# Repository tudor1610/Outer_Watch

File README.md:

<small>Copyright @Tudor Brandibur 2025-2026</small>

# Outer Watch

This repository contains the project for Outer_Watch, a smart watch based on the nRF52840 microcontroller, designed for power efficiency and Bluetooth Low Energy (BLE) connectivity.

## 1. Block diagram

## 2. BOM
| Designator | Qty | Component | Package | Description | Part number | Datasheet/Link |
| :--- | :---: | :--- | :--- | :--- | :--- | :--- |
| U1 | 1 | nRF52840 | aQFN-73 | Main Bluetooth 5.4 SoC | [C190733](https://www.lcsc.com/product-detail/C190733.html) | [View](https://www.lcsc.com/product-detail/C190733.html) |
| IC1 | 1 | BQ25180YBGR | DSBGA-8 | Battery Charge Management IC | [C5186637](https://www.lcsc.com/product-detail/C5186637.html) | [View](https://www.lcsc.com/product-detail/C5186637.html) |
| IC9 | 1 | RT6160AWSC | WL-CSP-15 | High-Efficiency Buck-Boost | [C464871](https://www.lcsc.com/product-detail/C464871.html) | [View](https://www.lcsc.com/product-detail/C464871.html) |
| IC3 | 1 | BMA423 | LGA-12 | 3-axis Accelerometer | [C128221](https://www.lcsc.com/product-detail/C128221.html) | [View](https://www.lcsc.com/product-detail/C128221.html) |
| U3 | 1 | MAX17048G+T10 | TDFN-8 | Battery Fuel Gauge | [C51509](https://www.lcsc.com/product-detail/C51509.html) | [View](https://www.lcsc.com/product-detail/C51509.html) |
| IC2 | 1 | DRV2605YZFR | DSBGA-9 | Haptic Driver | [C60367](https://www.lcsc.com/product-detail/C60367.html) | [View](https://www.lcsc.com/product-detail/C60367.html) |
| J4 | 1 | KH-TYPE-C-16P | SMD | USB-C 16-Pin Connector | [C3111425](https://www.lcsc.com/product-detail/C3111425.html) | [View](https://www.lcsc.com/product-detail/C3111425.html) |
| J1 | 1 | 503480-2400 | SMD | 24-Pin FPC Connector | [C193568](https://www.lcsc.com/product-detail/C193568.html) | [View](https://www.lcsc.com/product-detail/C193568.html) |
| ANT1 | 1 | 2450AT18B100E | 1206 | 2.4GHz Chip Antenna | [C96245](https://www.lcsc.com/product-detail/C96245.html) | [View](https://www.lcsc.com/product-detail/C96245.html) |
| D3 | 1 | USBLC6-2SC6Y | SOT-23-6 | ESD Protection | [C314115](https://www.lcsc.com/product-detail/C314115.html) | [View](https://www.lcsc.com/product-detail/C314115.html) |
| Q1 | 1 | DMG2305UX-7 | SOT-23 | P-Channel MOSFET | [C131015](https://www.lcsc.com/product-detail/C131015.html) | [View](https://www.lcsc.com/product-detail/C131015.html) |
| Q3 | 1 | SI1308EDL-T1-GE3 | SOT-323 | N-Channel MOSFET 30V | [C139044](https://www.lcsc.com/product-detail/C139044.html) | [View](https://www.lcsc.com/product-detail/C139044.html) |
| D2, D4, D5 | 3 | MBR0530 | SOD-123 | Schottky Rectifier | [C2053](https://www.lcsc.com/product-detail/C2053.html) | [View](https://www.lcsc.com/product-detail/C2053.html) |
| X1 | 1 | ABM11-27MHz | 2016 | 27MHz HF Crystal | [C529322](https://www.lcsc.com/product-detail/C529322.html) | [View](https://www.lcsc.com/product-detail/C529322.html) |
| X2 | 1 | LFXTAL061361 | 3215 | 32.768kHz RTC Crystal | [C104780](https://www.lcsc.com/product-detail/C104780.html) | [View](https://www.lcsc.com/product-detail/C104780.html) |
| L7 | 1 | MLP2016SR47M | 0806 | 0.47uH Power Inductor | [C45943](https://www.lcsc.com/product-detail/C45943.html) | [View](https://www.lcsc.com/product-detail/C45943.html) |
| L5 | 1 | 744043680 | SMD | 68uH Shielded Inductor | [C19438](https://www.lcsc.com/product-detail/C19438.html) | [View](https://www.lcsc.com/product-detail/C19438.html) |
| L2, L3 | 2 | ATFC-0402-3N3 | 0402 | 3.3nH High Q Inductor | [C529323](https://www.lcsc.com/product-detail/C529323.html) | [View](https://www.lcsc.com/product-detail/C529323.html) |
| R-Group | 15 | CPF0201D7K68C1 | 0201 | Precision Resistors | [C420120](https://www.lcsc.com/product-detail/C420120.html) | [View](https://www.lcsc.com/product-detail/C420120.html) |
| C-0402 | 25 | C0402C333J4REC | 0402 | MLCC Capacitors | [C418932](https://www.lcsc.com/product-detail/C418932.html) | [View](https://www.lcsc.com/product-detail/C418932.html) |
| C-0201 | 26 | 02016D105KAT2A | 0201 | X5R 1.0uF Capacitors | [C293021](https://www.lcsc.com/product-detail/C293021.html) | [View](https://www.lcsc.com/product-detail/C293021.html) |
| C-Ultra | 4 | GRM011R60J152 | 01005 | Ultra-Small Capacitors | [C293022](https://www.lcsc.com/product-detail/C293022.html) | [View](https://www.lcsc.com/product-detail/C293022.html) |

## 3. Hardware Description

#### Modules and Functionality
Microcontroller (SoC): nRF52840 (Cortex-M4F at 64MHz). It offers native support for USB, Bluetooth 5, and ultra-low power consumption in sleep modes.

#### Sensors
Integrated motion sensor (IMU) for features like "Lift to Wake" and step counting.

#### Power Management
Battery charging is handled by the TP4056 circuit powered via USB-C. Voltage is regulated to 3.3V through the RT9193 LDO regulator.

#### Communication Interfaces
I2C: Used for the Display and IMU (Standard 400kHz speed).

SWD: Programming and debugging interface (SWDIO and SWDCLK pins).

USB: For charging and data communication/DFU.

### Power Consumption (Estimation)
Deep Sleep (System OFF): ~3uA (nRF52840) + ~2uA (IMU sleep) = ~5uA.

Active Mode (Screen ON + BLE): ~15mA - 20mA.

Battery Life: With a 200mAh battery, under mixed usage, the watch can operate between 5 to 10 days.

## 4. Hardware Mapping & Pin Configuration
The nRF52840 acts as the central brain. Below is the pin allocation strategy used to balance signal integrity, power consumption, and peripheral speed.
1. Communication Buses (I2C & SPI)

- Display (SPI): P0.17 (SCK), P0.20 (MOSI), P0.15 (CS), P0.22 (DC), P0.24 (RST)
- Sensors & Power (I2C): P0.26 (SDA), P0.27 (SCL)

2. Specialized Integrated Circuits (ICs)

- BMA423 (Accelerometer): P0.11 (INT1): Used for Wake-on-Motion. This allows the nRF52840 to stay in "System ON" low-power mode until a wrist tilt or tap is detected.

- MAX17048 (Fuel Gauge): 0.26/P0.27: Reads battery VCELL and SOC (State of Charge). No external sense resistor is needed due to the ModelGauge algorithm.

- BQ25180 (Charger): P0.13 (INT): Signals charging status changes (cable connected, charging complete).

- DRV2605L (Haptic Driver): P0.14 (EN): Enables the chip. Controlled via I2C to trigger complex ERM/LRA vibration patterns for notifications.

3. Power & Interaction
- Navigation Switches (SW_UP, SW_DW, SW_ENT): P1.02, P1.04, P1.06: Connected to GPIOs with internal Pull-Up resistors. These pins on Port 1 are used to keep Port 0 free for high-speed serial traces.

- USB Interface: D+ / D-: Dedicated hardware pins on the nRF52840. Used for the USB stack (CDC/MSC) without consuming standard GPIOs.

4. RF & Clock (Critical Traces)

- 2.4GHz Antenna: ANT

- HF Crystal (27MHz): XC1, XC2

- LF Crystal (32.768kHz): P0.00, P0.01

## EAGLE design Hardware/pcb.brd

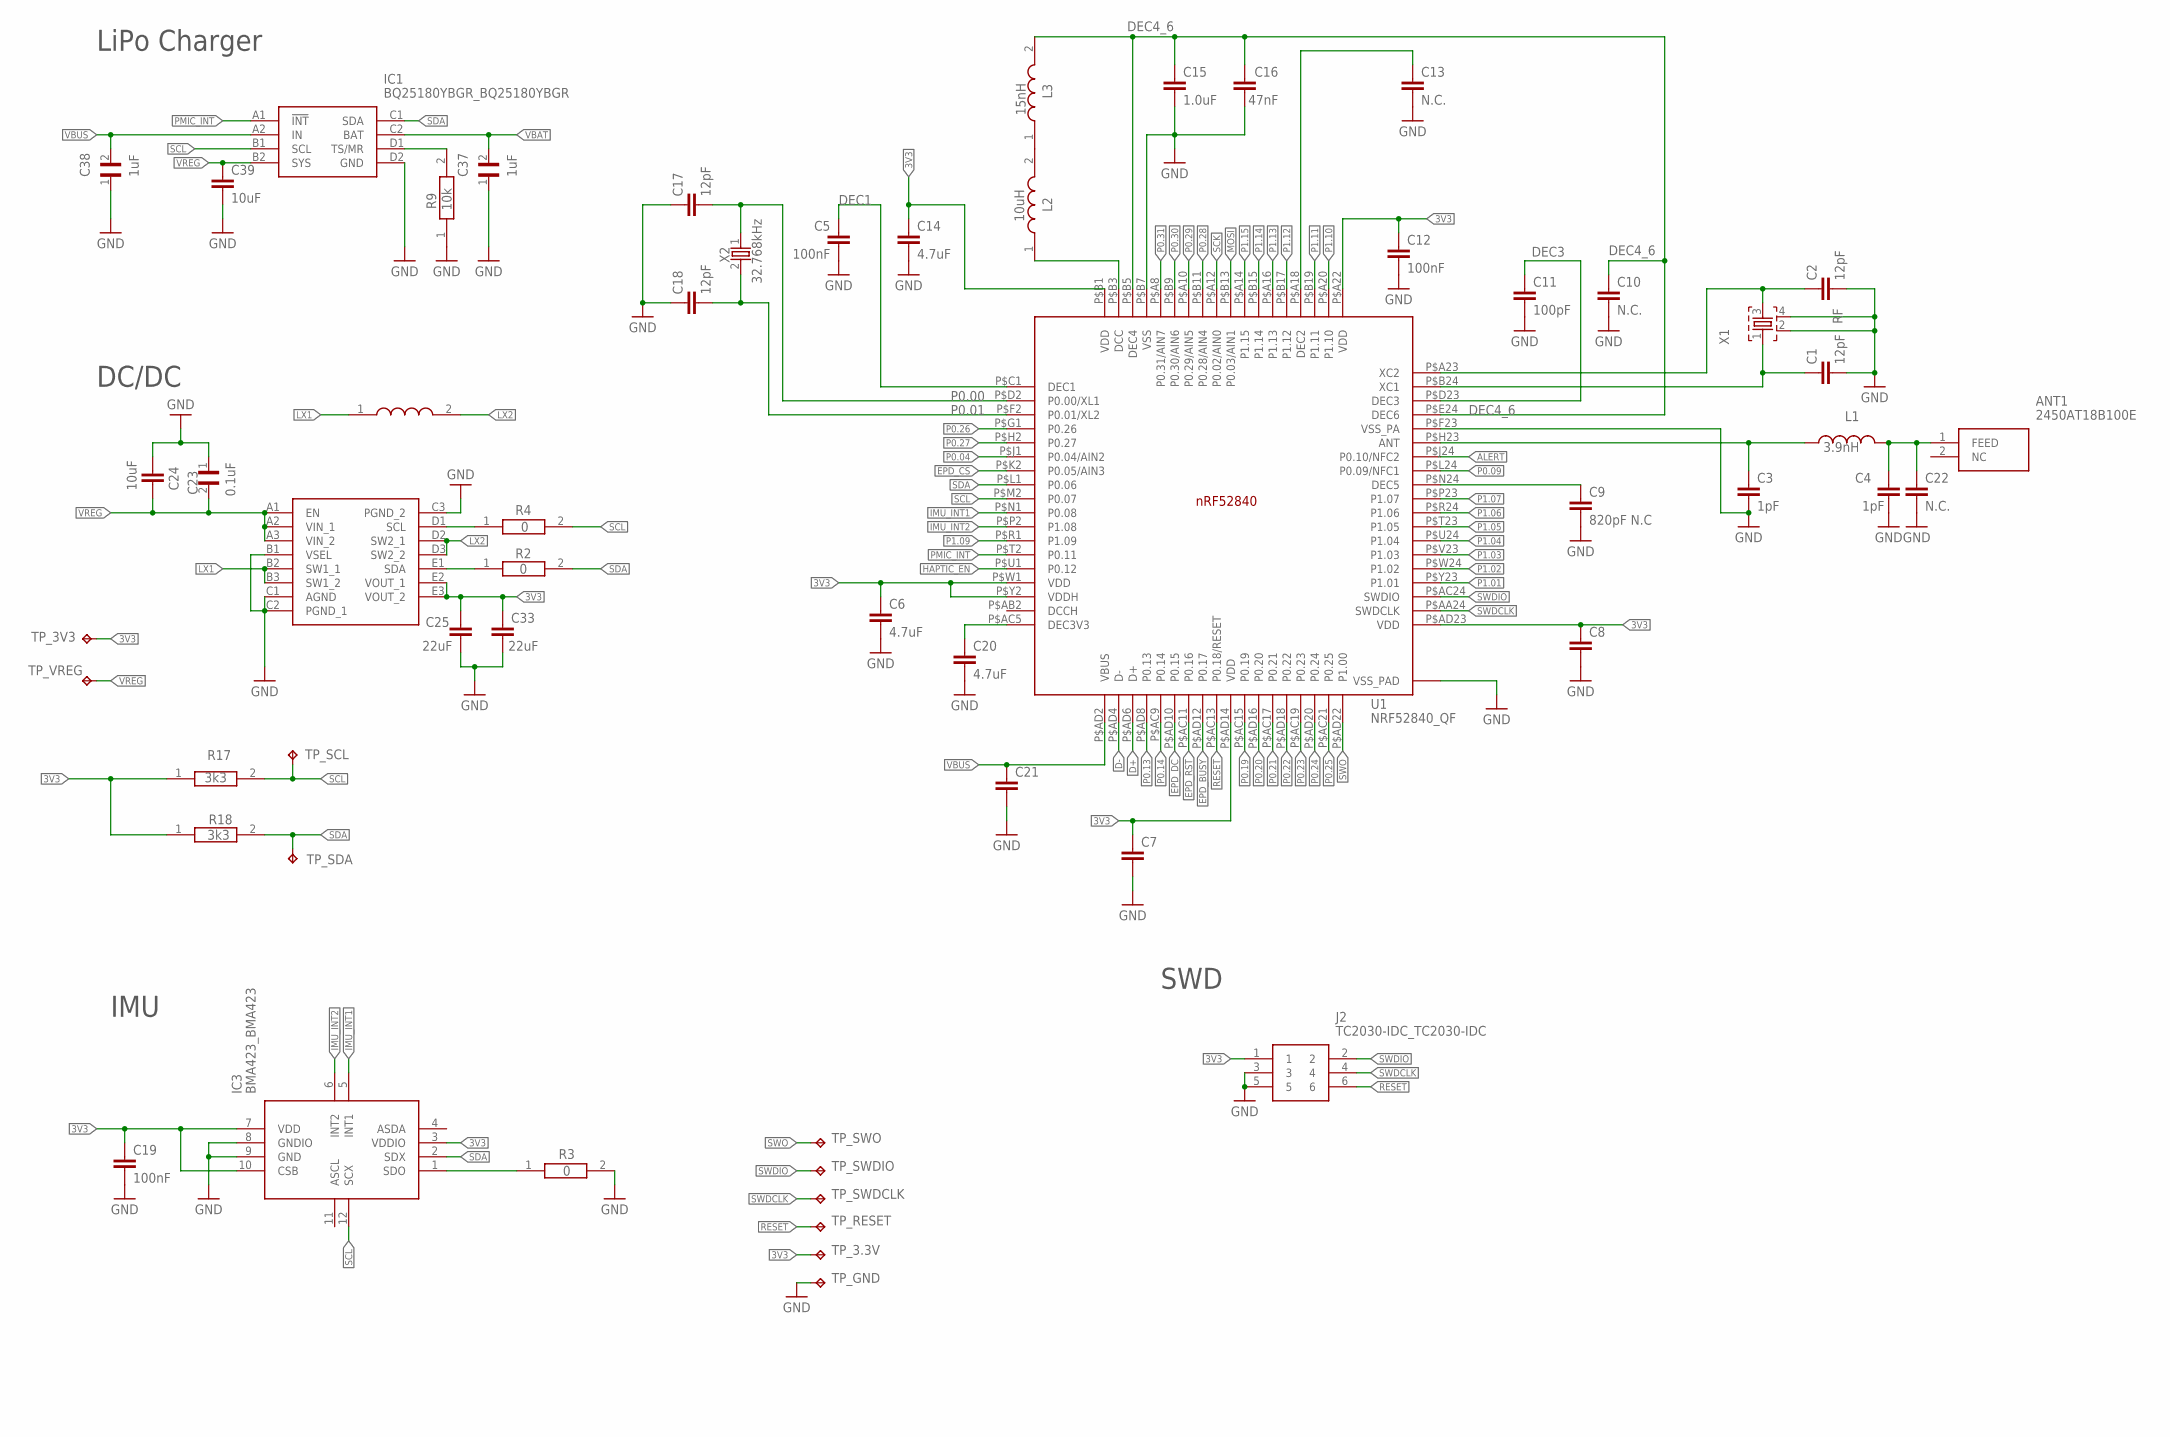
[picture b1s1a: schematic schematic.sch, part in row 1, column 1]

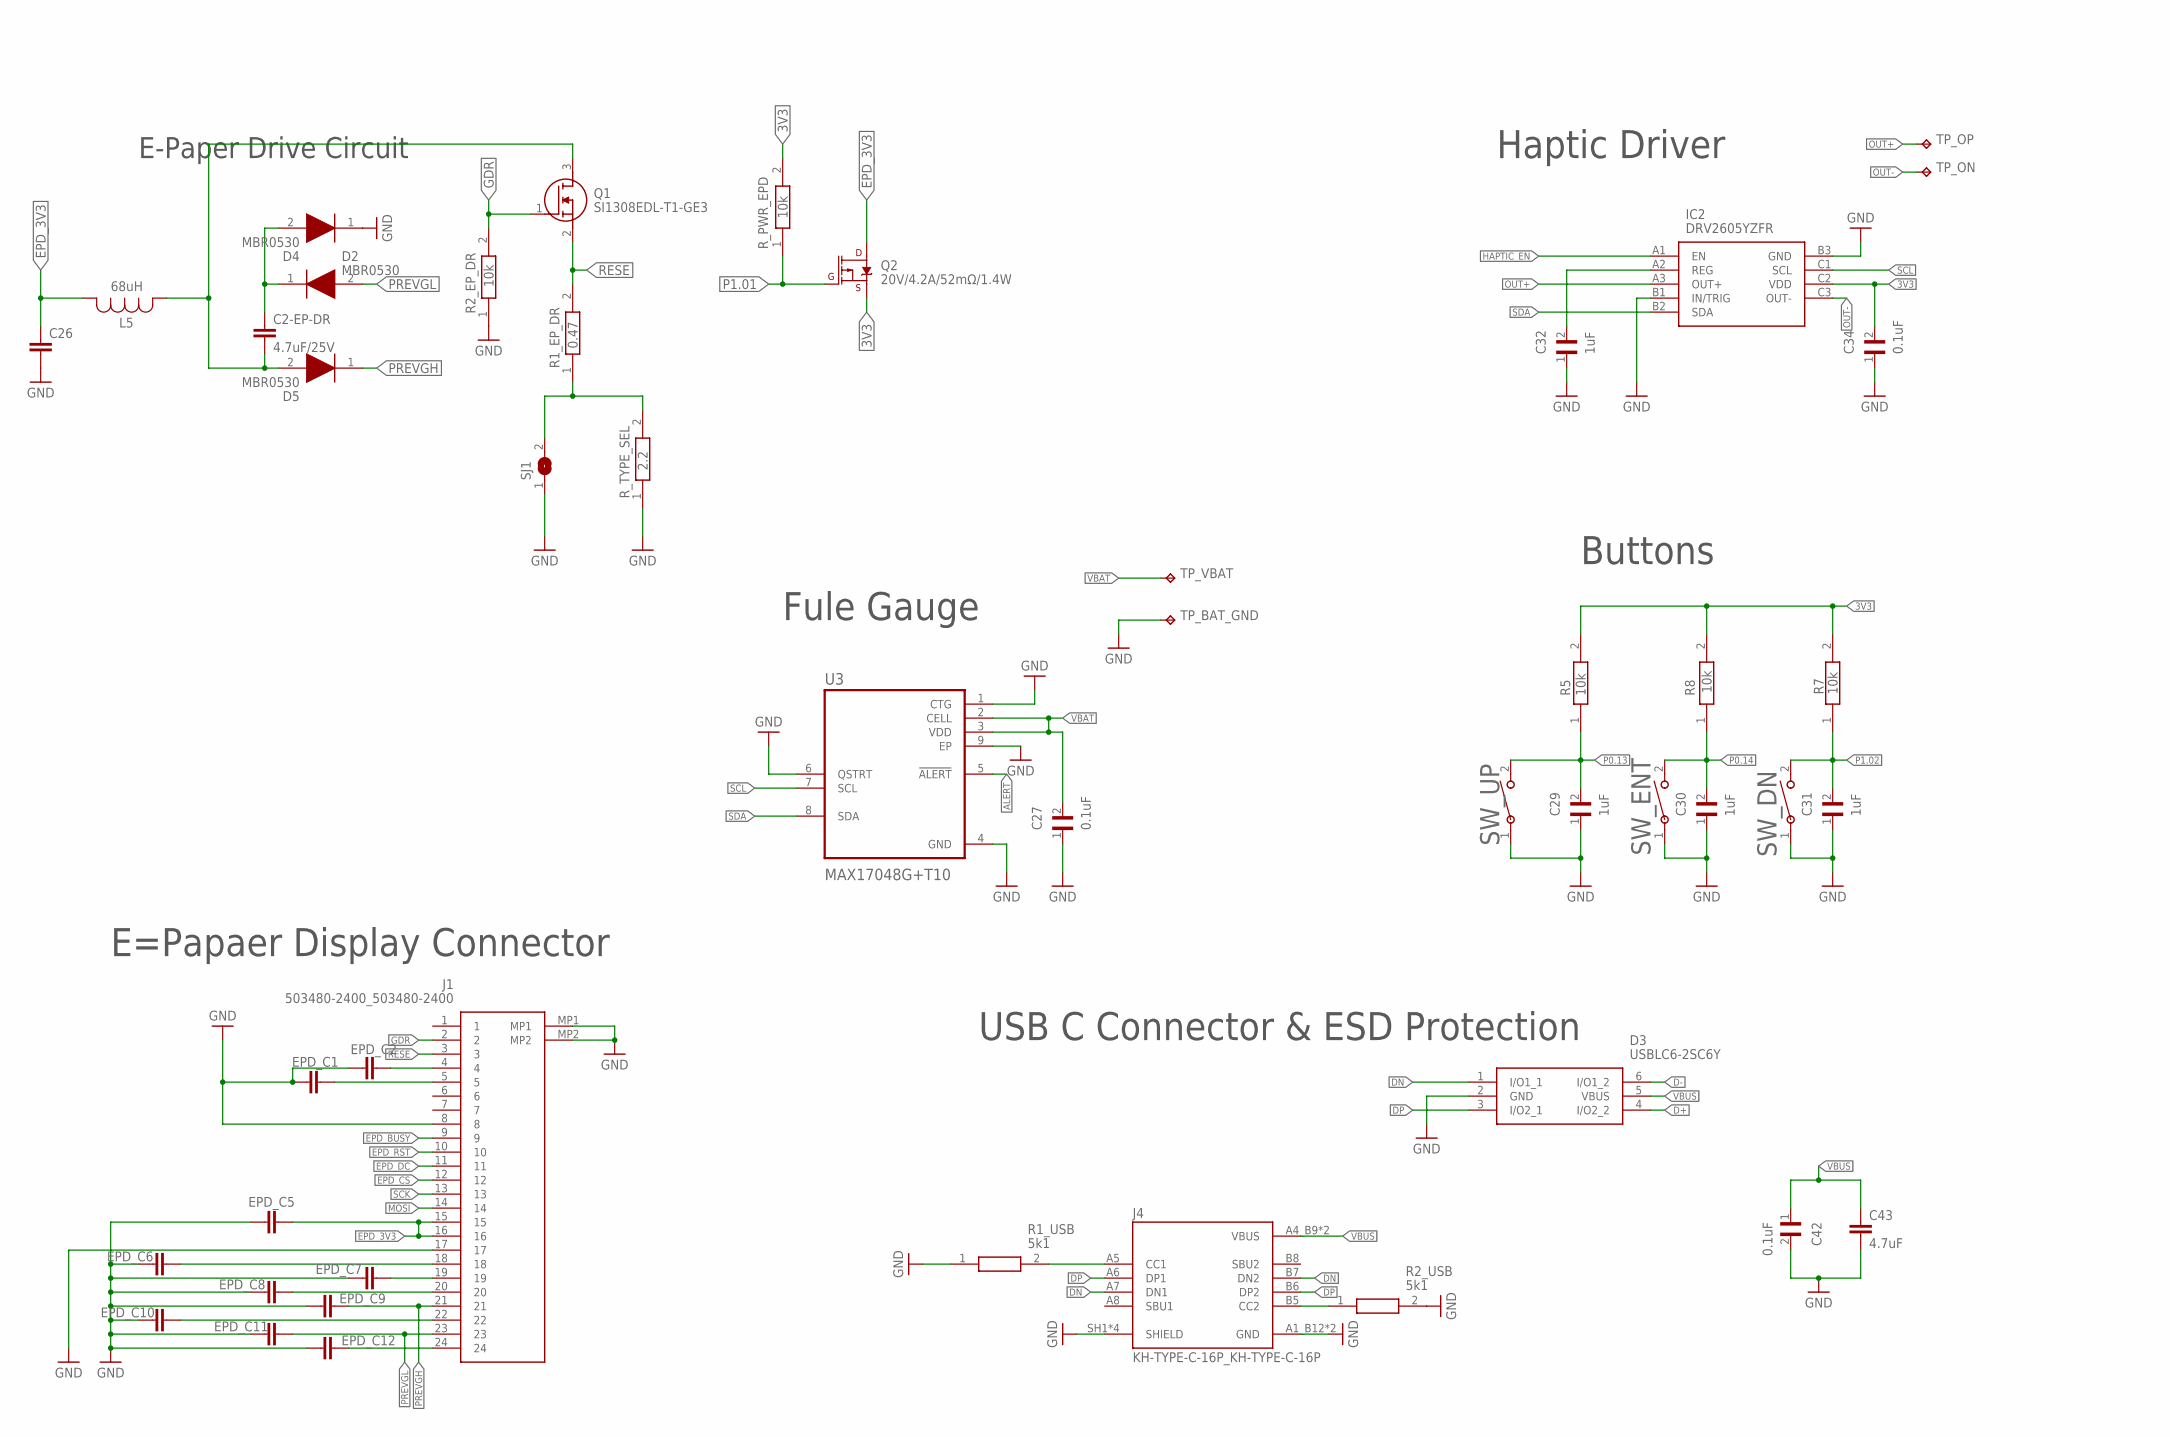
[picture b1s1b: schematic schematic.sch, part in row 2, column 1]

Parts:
ANT1: 2450AT18B100E; 2450AT18B100E_ANTC3216X140N
C1, C2, C17, C18: 12pF; NORDIC_NRF_3_RESC0201_L
C2-EP-DR: 4.7uF/25V; ESP32_C6_LIBRARY_1_ESP32_WROVER_EAGLE-LTSPICE_C0402
C3, C4: 1pF; NORDIC_NRF_3_RESC0201_L
C5, C12, C19: 100nF; NORDIC_NRF_3_RESC0201_L
C6, C14, C20: 4.7uF; ESP32_C6_LIBRARY_1_ESP32_WROVER_EAGLE-LTSPICE_C0402
C7, C21, C26: ESP32_C6_LIBRARY_1_ESP32_WROVER_EAGLE-LTSPICE_CC0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; ESP32_C6_LIBRARY_1_ESP32_WROVER_EAGLE-LTSPICE_C0402
C8: NORDIC_NRF_3_CAPACITOR_0201_L; NORDIC_NRF_3_RESC0201_L
C9: 820pF N.C; NORDIC_NRF_3_RESC0201_L
C10, C22: N.C.; NORDIC_NRF_3_RESC0201_L
C11: 100pF; NORDIC_NRF_3_RESC0201_L
C13: N.C.; ESP32_C6_LIBRARY_1_ESP32_WROVER_EAGLE-LTSPICE_C0402
C15: 1.0uF; ESP32_C6_LIBRARY_1_ESP32_WROVER_EAGLE-LTSPICE_C0402
C16: 47nF; NORDIC_NRF_3_RESC0201_L
C23, C27, C34, C42: 0.1uF; GRM011R60J152KE01L_2_CAPC0201X13N
C24, C39: 10uF; ESP32_C6_LIBRARY_1_ESP32_WROVER_EAGLE-LTSPICE_C0402
C25, C33: 22uF; ESP32_C6_LIBRARY_1_ESP32_WROVER_EAGLE-LTSPICE_C0402
C29, C30, C31, C32, C37, C38: 1uF; GRM011R60J152KE01L_2_CAPC0201X13N
C43: 4.7uF; NORDIC_NRF_3_RESC0402_L
D2, D4, D5: MBR0530; ESP32_C6_LIBRARY_5_SOD3716X135N
D3: USBLC6-2SC6Y; ESP32_C6_LIBRARY_3_SOT95P280X145-6N
EPD_C1, EPD_C2, EPD_C5, EPD_C6, EPD_C7, EPD_C8, EPD_C9, EPD_C10, EPD_C11, EPD_C12: NORDIC_NRF_3_CAPACITOR_0402_L; NORDIC_NRF_3_RESC0402_L
IC1: BQ25180YBGR_BQ25180YBGR; BQ25180YBGR_BGA8C40P2X4_100X155X50
IC2: DRV2605YZFR; DRV2605YZFR_BGA9C50P3X3_144X144X62
IC3: BMA423_BMA423
IC9: RT6160AWSC_RT6160AWSC; RT6160AWSC_BGA15C40P3X5_140X230X60
J1: 503480-2400_503480-2400; 503480-2400_5034802400
J2: TC2030-IDC_TC2030-IDC; TC2030-IDC_TC2030IDC
J4: KH-TYPE-C-16P_KH-TYPE-C-16P; KH-TYPE-C-16P_KINGHELM_KH-TYPE-C-16P
L1: 3.9nH; NORDIC_NRF_2_RESC0805_N
L2: 10uH; MLP2016SR47MT0S1_INDC2016X100N
L3: 15nH; MLP2016SR47MT0S1_INDC2016X100N
L5: 68uH; ESP32_C6_LIBRARY_2_IND_4828-WE-TPC_WRE
L7: MLP2016SR47MT0S1_FTC252012SR47MBCA; MLP2016SR47MT0S1_INDC2016X100N
Q1: SI1308EDL-T1-GE3; ESP32_C6_LIBRARY_6_SOT65P210X110-3N
Q2: 20V/4.2A/52mΩ/1.4W; ESP32_C6_LIBRARY_4_ESP32_C6_LIBRARY_4_ESP32_C6_LIBRARY_4_ES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
R1_EP_DR: 0.47; CPF0201D7K68C1_0201
R1_USB, R2_USB: 5k1; ERA-1AEB3401C_0201
R2, R3, R4: 0; CPF0201D7K68C1_0201
R2_EP_DR, R9: 10k; CPF0201D7K68C1_0201
R5, R7, R8: 10k; ERA-1AEB3401C_0201
R17, R18: 3k3; CPF0201D7K68C1_0201
R_PWR_EPD: 10k; CPF0201D7K68C1_0201
R_TYPE_SEL: 2.2; CPF0201D7K68C1_0201
SJ1: ESP32_C6_LIBRARY_7_JUMPER_SJ
SW_DN: 2025-10-22_07-23-44_LIBRARY_EVP-AKE31ASW_EVP-AKE3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; 2025-10-22_07-23-44_LIBRARY_SW_EVP-AKE31A_PAN
SW_ENT: 2025-10-22_07-23-44_LIBRARY_EVP-AKE31ASW_EVP-AKE3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; 2025-10-22_07-23-44_LIBRARY_SW_EVP-AKE31A_PAN
SW_UP: 2025-10-22_07-23-44_LIBRARY_EVP-AKE31ASW_EVP-AKE3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; 2025-10-22_07-23-44_LIBRARY_SW_EVP-AKE31A_PAN
TP_3.3V: HECTOR_WATCH_1_TPTP20R; HECTOR_WATCH_1_TP20R
TP_3V3: TP_3V3; HECTOR_WATCH_1_TP20R
TP_BAT_GND: HECTOR_WATCH_1_TPTP20R; HECTOR_WATCH_1_TP20R
TP_GND: HECTOR_WATCH_1_TPTP20R; HECTOR_WATCH_1_TP20R
TP_ON: HECTOR_WATCH_1_TPTP20R; HECTOR_WATCH_1_TP20R
TP_OP: HECTOR_WATCH_1_TPTP20R; HECTOR_WATCH_1_TP20R
TP_RESET: HECTOR_WATCH_1_TPTP20R; HECTOR_WATCH_1_TP20R
TP_SCL: HECTOR_WATCH_1_TPTP20R; HECTOR_WATCH_1_TP20R
TP_SDA: HECTOR_WATCH_1_TPTP20R; HECTOR_WATCH_1_TP20R
TP_SWDCLK: HECTOR_WATCH_1_TPTP20R; HECTOR_WATCH_1_TP20R
TP_SWDIO: HECTOR_WATCH_1_TPTP20R; HECTOR_WATCH_1_TP20R
TP_SWO: HECTOR_WATCH_1_TPTP20R; HECTOR_WATCH_1_TP20R
TP_VBAT: HECTOR_WATCH_1_TPTP20R; HECTOR_WATCH_1_TP20R
TP_VREG: HECTOR_WATCH_1_TPTP20R; HECTOR_WATCH_1_TP20R
U1: NRF52840_QF; NORDIC_NRF_4_AQFN50P700X700X85_HS-74N
U3: MAX17048G+T10; ESP32_C6_LIBRARY_SON50P200X200X80-9N
X1: NORDIC_NRF_XTAL_32MHZ; NORDIC_NRF_BT-XTAL_2016_N
X2: 32.768kHz; NORDIC_NRF_1_XTAL_3215_N

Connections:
3V3: C6.1, C7.1, C8.1, C12.1, C14.1, C19.1, C25.1, C33.1, C34.2, IC2.C2 (VDD), IC3.3 (VDDIO), IC3.7 (VDD), IC3.10 (CSB), IC9.E2 (VOUT_1), IC9.E3 (VOUT_2), J2.1, Q2.2 (S), R5.2, R7.2, R8.2, R17.1, R18.1, R_PWR_EPD.2, TP_3.3V.TP, TP_3V3.TP, U1.P$A22 (VDD), U1.P$AD14 (VDD), U1.P$AD23 (VDD), U1.P$B1 (VDD), U1.P$W1 (VDD), U1.P$Y2 (VDDH)
ALERT: U1.P$J24 (P0.10/NFC2), U3.5 (!ALERT)
D+: D3.4 (I/O2_2), U1.P$AD6 (D+)
D-: D3.6 (I/O1_2), U1.P$AD4 (D-)
DEC1: C5.2, U1.P$C1 (DEC1)
DEC3: C11.1, U1.P$D23 (DEC3)
DEC4_6: C10.1, C15.1, C16.2, L3.2, U1.P$B5 (DEC4), U1.P$E24 (DEC6)
DN: D3.1 (I/O1_1), J4.A7 (DN1), J4.B7 (DN2)
DP: D3.3 (I/O2_1), J4.A6 (DP1), J4.B6 (DP2)
EPD_3V3: C26.1, EPD_C5.2, J1.15, J1.16, L5.1, Q2.3 (D)
EPD_BUSY: J1.9, U1.P$AD12 (P0.17)
EPD_CS: J1.12, U1.P$K2 (P0.05/AIN3)
EPD_DC: J1.11, U1.P$AD10 (P0.15)
EPD_RST: J1.10, U1.P$AC11 (P0.16)
GDR: J1.2, Q1.1 (G), R2_EP_DR.2
GND: C1.2, C2.2, C3.2, C4.2, C5.1, C6.2, C7.2, C8.2, C9.2, C10.2, C11.2, C12.2, C13.2, C14.2, C15.2, C16.1, C17.1, C18.1, C19.2, C20.2, C21.2, C22.2, C23.1, C24.1, C25.2, C26.2, C27.1, C29.1, C30.1, C31.1, C32.1, C33.2, C34.1, C37.1, C38.1, C39.2, C42.2, C43.2, D3.2 (GND), D4.1 (K), EPD_C1.1, EPD_C2.1, EPD_C5.1, EPD_C6.1, EPD_C7.1, EPD_C8.1, EPD_C9.1, EPD_C10.1, EPD_C11.1, EPD_C12.1, IC1.D2 (GND), IC2.B1 (IN/TRIG), IC2.B3 (GND), IC3.8 (GNDIO), IC3.9 (GND), IC9.B1 (VSEL), IC9.C1 (AGND), IC9.C2 (PGND_1), IC9.C3 (PGND_2), J1.8, J1.17, J1.MP1, J1.MP2, J2.3, J2.5, J4.A1_B12 (GND), J4.A12_B1 (GND), J4.SH1 (SHIELD), J4.SH2 (SHIELD), J4.SH3 (SHIELD), J4.SH4 (SHIELD), R1_USB.1, R2_EP_DR.1, R2_USB.2, R3.2, R9.1, R_TYPE_SEL.1, SJ1.1, SW_DN.1, SW_ENT.1, SW_UP.1, TP_BAT_GND.TP, TP_GND.TP, U1.P$74 (VSS_PAD), U1.P$75 (VSS_PAD), U1.P$76 (VSS_PAD), U1.P$77 (VSS_PAD), U1.P$78 (VSS_PAD), U1.P$79 (VSS_PAD), U1.P$80 (VSS_PAD), U1.P$81 (VSS_PAD), U1.P$82 (VSS_PAD), U1.P$83 (VSS_PAD), U1.P$84 (VSS_PAD), U1.P$85 (VSS_PAD), U1.P$86 (VSS_PAD), U1.P$87 (VSS_PAD), U1.P$88 (VSS_PAD), U1.P$89 (VSS_PAD), U1.P$90 (VSS_PAD), U1.P$B7 (VSS), U1.P$F23 (VSS_PA), U3.1 (CTG), U3.4 (GND), U3.6 (QSTRT), U3.9 (EP), X1.2, X1.4
HAPTIC_EN: IC2.A1 (EN), U1.P$U1 (P0.12)
IMU_INT1: IC3.5 (INT1), U1.P$N1 (P0.08)
IMU_INT2: IC3.6 (INT2), U1.P$P2 (P1.08)
LX1: IC9.B2 (SW1_1), IC9.B3 (SW1_2), L7.1
LX2: IC9.D2 (SW2_1), IC9.D3 (SW2_2), L7.2
MOSI: J1.14, U1.P$B13 (P0.03/AIN1)
unnamed: C2.1, U1.P$A23 (XC2), X1.3
unnamed: IC3.1 (SDO), R3.1
unnamed: C1.1, U1.P$B24 (XC1), X1.1
unnamed: C3.1, L1.1, U1.P$H23 (ANT)
unnamed: IC1.D1 (TS/MR), R9.2
unnamed: L2.2, L3.1
unnamed: L2.1, U1.P$B3 (DCC)
unnamed: EPD_C2.2, J1.4
unnamed: IC9.D1 (SCL), R4.1
unnamed: C13.1, U1.P$A18 (DEC2)
unnamed: C9.1, U1.P$N24 (DEC5)
unnamed: IC9.E1 (SDA), R2.1
unnamed: C2-EP-DR.2, D5.2 (A), L5.2, Q1.3 (D)
unnamed: C2-EP-DR.1, D2.1 (K), D4.2 (A)
unnamed: EPD_C1.2, J1.5
unnamed: C32.2, IC2.A2 (REG)
unnamed: J4.A5 (CC1), R1_USB.2
unnamed: C20.1, U1.P$AC5 (DEC3V3)
unnamed: R1_EP_DR.1, R_TYPE_SEL.2, SJ1.2
unnamed: J4.B5 (CC2), R2_USB.1
unnamed: EPD_C6.2, J1.18
unnamed: EPD_C7.2, J1.19
unnamed: EPD_C12.2, J1.24
unnamed: EPD_C10.2, J1.22
unnamed: EPD_C8.2, J1.20
OUT+: IC2.A3 (OUT+), TP_OP.TP
OUT-: IC2.C3 (OUT-), TP_ON.TP
P0.00: C17.2, U1.P$D2 (P0.00/XL1), X2.1
P0.01: C18.2, U1.P$F2 (P0.01/XL2), X2.2
P0.04: U1.P$J1 (P0.04/AIN2)
P0.09: U1.P$L24 (P0.09/NFC1)
P0.13: C29.2, R5.1, SW_UP.2, U1.P$AD8 (P0.13)
P0.14: C30.2, R8.1, SW_ENT.2, U1.P$AC9 (P0.14)
P0.19: U1.P$AC15 (P0.19)
P0.20: U1.P$AD16 (P0.20)
P0.21: U1.P$AC17 (P0.21)
P0.22: U1.P$AD18 (P0.22)
P0.23: U1.P$AC19 (P0.23)
P0.24: U1.P$AD20 (P0.24)
P0.25: U1.P$AC21 (P0.25)
P0.26: U1.P$G1 (P0.26)
P0.27: U1.P$H2 (P0.27)
P0.28: U1.P$B11 (P0.28/AIN4)
P0.29: U1.P$A10 (P0.29/AIN5)
P0.30: U1.P$B9 (P0.30/AIN6)
P0.31: U1.P$A8 (P0.31/AIN7)
P1.01: Q2.1 (G), R_PWR_EPD.1, U1.P$Y23 (P1.01)
P1.02: C31.2, R7.1, SW_DN.2, U1.P$W24 (P1.02)
P1.03: U1.P$V23 (P1.03)
P1.04: U1.P$U24 (P1.04)
P1.05: U1.P$T23 (P1.05)
P1.06: U1.P$R24 (P1.06)
P1.07: U1.P$P23 (P1.07)
P1.09: U1.P$R1 (P1.09)
P1.10: U1.P$A20 (P1.10)
P1.11: U1.P$B19 (P1.11)
P1.12: U1.P$B17 (P1.12)
P1.13: U1.P$A16 (P1.13)
P1.14: U1.P$B15 (P1.14)
P1.15: U1.P$A14 (P1.15)
PMIC_INT: IC1.A1 (!INT), U1.P$T2 (P0.11)
PREVGH: D5.1 (K), EPD_C9.2, J1.21
PREVGL: D2.2 (A), EPD_C11.2, J1.23
RESE: J1.3, Q1.2 (S), R1_EP_DR.2
RESET: J2.6, TP_RESET.TP, U1.P$AC13 (P0.18/RESET)
RF: ANT1.1 (FEED), C4.1, C22.1, L1.2
SCK: J1.13, U1.P$A12 (P0.02/AIN0)
SCL: IC1.B1 (SCL), IC2.C1 (SCL), IC3.12 (SCX), R4.2, R17.2, TP_SCL.TP, U1.P$M2 (P0.07), U3.7 (SCL)
SDA: IC1.C1 (SDA), IC2.B2 (SDA), IC3.2 (SDX), R2.2, R18.2, TP_SDA.TP, U1.P$L1 (P0.06), U3.8 (SDA)
SWDCLK: J2.4, TP_SWDCLK.TP, U1.P$AA24 (SWDCLK)
SWDIO: J2.2, TP_SWDIO.TP, U1.P$AC24 (SWDIO)
SWO: TP_SWO.TP, U1.P$AD22 (P1.00)
VBAT: C27.2, C37.2, IC1.C2 (BAT), TP_VBAT.TP, U3.2 (CELL), U3.3 (VDD)
VBUS: C21.1, C38.2, C42.1, C43.1, D3.5 (VBUS), IC1.A2 (IN), J4.A4_B9 (VBUS), J4.A9_B4 (VBUS), U1.P$AD2 (VBUS)
VREG: C23.2, C24.2, C39.1, IC1.B2 (SYS), IC9.A1 (EN), IC9.A2 (VIN_1), IC9.A3 (VIN_2), TP_VREG.TP

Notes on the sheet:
LiPo Charger
DC/DC
IMU
SWD
E-Paper Drive Circuit
Haptic Driver
Fule Gauge
Buttons
USB C Connector & ESD Protection
E=Papaer Display Connector

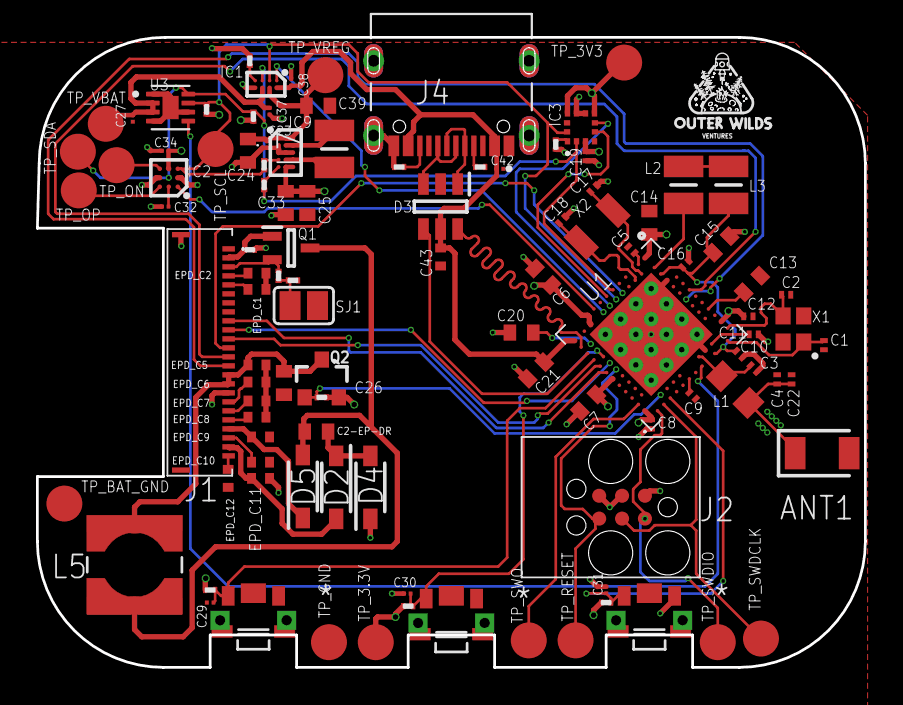
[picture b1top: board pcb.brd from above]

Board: 4 copper layers, 46.0 x 35.0 mm, 105 parts (0 on the bottom side), 70 nets.

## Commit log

2026-04-10 Upload hardware files
2026-04-15 Uploaded PNGs of the board and 3d design
2026-04-20 Add README
2026-04-20 Fixed issues

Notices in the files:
parts and their libraries:
COPYRIGHT: Copyright (C) 2024 Ultra Librarian. All rights reserved.
COPYRIGHT: Copyright (C) 2025 Ultra Librarian. All rights reserved.
